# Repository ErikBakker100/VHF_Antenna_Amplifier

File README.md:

# VHF_Antenna_Amplifier
2mtr VHF Radio Antenna signal amplifier

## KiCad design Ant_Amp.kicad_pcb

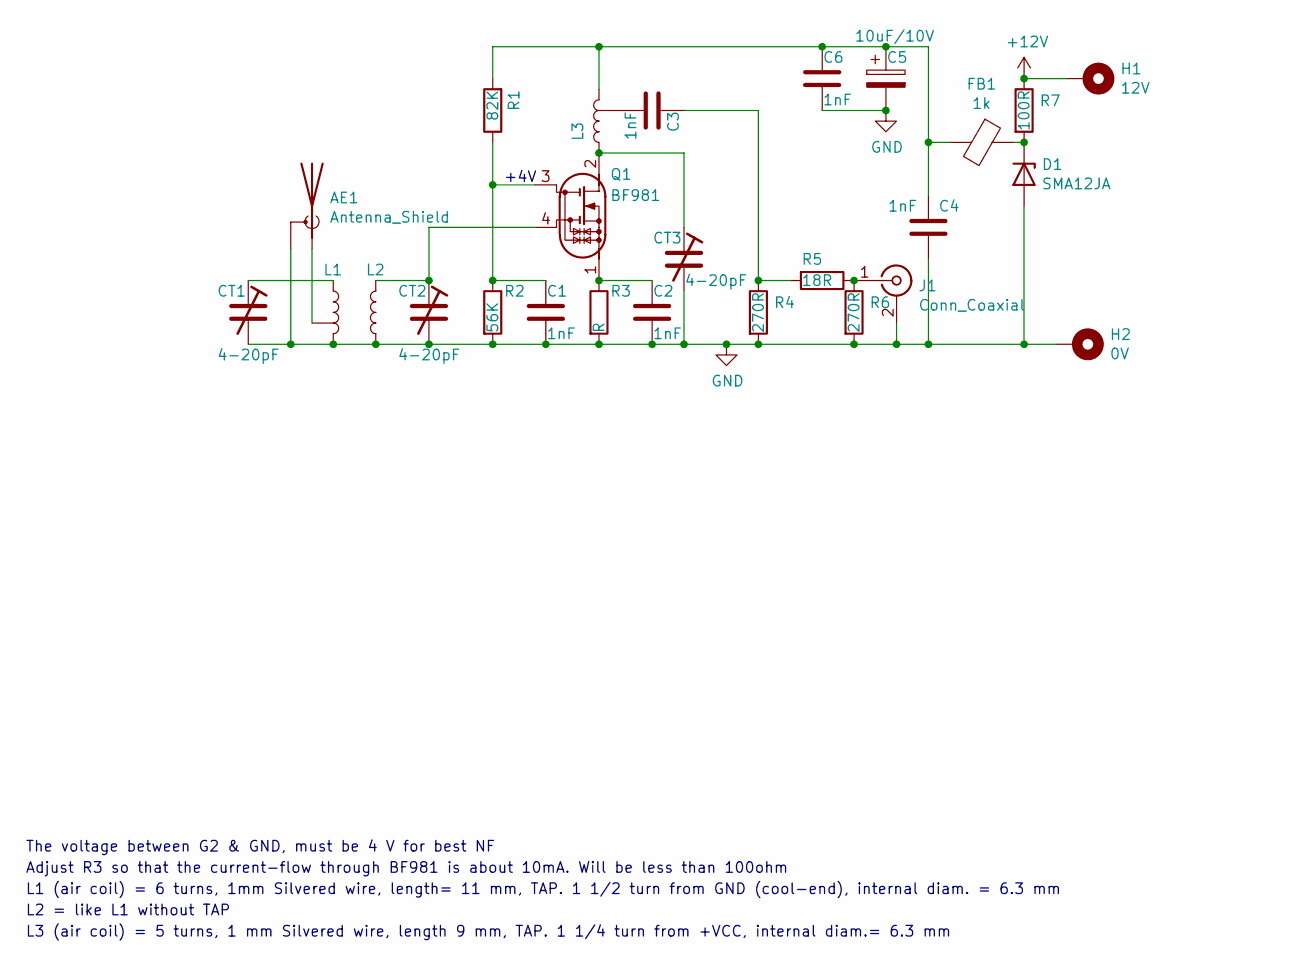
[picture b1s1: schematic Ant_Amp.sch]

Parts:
AE1: Antenna_Shield; Urydell_SMA_Haaks
C1, C2, C3, C4, C6: 1nF; C_0402_1005Metric
C5: 10uF/10V; C_1206_3216Metric
CT1, CT2, CT3: 4-20pF; C_Trimmer_Voltronics_JZ
D1: SMA12JA; D_SMA
FB1: 1k; R_0603_1608Metric
H1: 12V; NetTie-2_SMD_Pad2.0mm
H2: 0V; NetTie-2_SMD_Pad2.0mm
J1: Conn_Coaxial; Urydell_SMA_Haaks
L1: L-Tap; L_6T_11mm_intdiam6.3mm_1mm_wire_tap4.5TR
L2: L; L_6T_11mm_intdiam6.3mm_1mm_wire
L3: L-Tap; L_6T_11mm_intdiam6.3mm_1mm_wire_tap1.5T
Q1: BF981; SOT-103
R1: 82K; R_0603_1608Metric
R2: 56K; R_0603_1608Metric
R3: R; R_0603_1608Metric
R4, R6: 270R; R_0603_1608Metric
R5: 18R; R_0603_1608Metric
R7: 100R; R_2512_6332Metric

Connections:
+12V: H1.1, R7.1
GND: AE1.2 (Shield), C1.2, C2.2, C4.1, C5.2, C6.2, CT1.2, CT2.2, CT3.2, D1.2 (A), H2.1, J1.2 (Ext), L1.2, L2.1, R2.2, R3.2, R4.2, R6.2
unnamed: AE1.1 (A), L1.3
unnamed: C1.1, Q1.3 (G2), R1.1, R2.1
unnamed: C2.1, Q1.1 (S), R3.1
unnamed: C3.1, R4.1, R5.2
unnamed: C3.2, L3.3
unnamed: C4.2, C5.1, C6.1, FB1.2, L3.2, R1.2
unnamed: CT1.1, L1.1
unnamed: CT2.1, L2.2, Q1.4 (G1)
unnamed: CT3.1, L3.1, Q1.2 (D)
unnamed: D1.1 (K), FB1.1, R7.2
unnamed: J1.1 (In), R5.1, R6.1

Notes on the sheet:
L1 (air coil) = 6 turns, 1mm Silvered wire, length= 11 mm, TAP. 1 1/2 turn from GND (cool-end), internal diam. = 6.3 mm
L2 = like L1 without TAP
L3 (air coil) = 5 turns, 1 mm Silvered wire, length 9 mm, TAP. 1 1/4 turn from +VCC, internal diam.= 6.3 mm
Adjust R3 so that the current-flow through BF981 is about 10mA. Will be less than 100ohm
The voltage between G2 & GND, must be 4 V for best NF
+4V

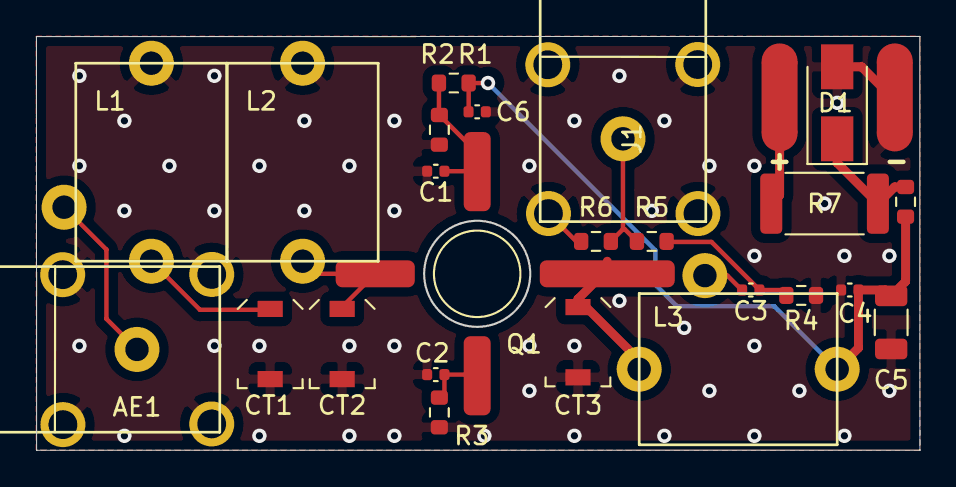
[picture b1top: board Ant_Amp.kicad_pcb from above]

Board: 2 copper layers, 49.0 x 22.9 mm, 26 parts (0 on the bottom side), 13 nets.

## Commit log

2021-02-14 21.02.14 start
2021-02-14 21.2.4_01
2021-02-16 16-2-2021_01
2021-02-17 172-2021_001
2021-02-17 17-2-2021_02
2021-02-17 17-2-21_02
2021-02-17 17-2-21_03
2021-02-20 Ver 1.0
2021-02-20 Gerber_update
2021-02-26 26-2-2021
